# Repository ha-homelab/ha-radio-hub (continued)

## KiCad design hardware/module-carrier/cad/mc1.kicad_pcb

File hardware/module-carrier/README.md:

# MC1 hardware

> **Historical MC1 revision.** The current [MC2 external-antenna build](../../docs/external-antennas.md) uses different modules, pins, flash layout and housing. Keep this material with MC1 boards only.

> **I²C correction, 20 October 2026:** the current MC1 firmware now requires
> DFR0627 **A1=1/A0=0**, UART1 **0x50/0x51**; reserve **0x50–0x57**.
> Older frozen drawings/ledgers showing A1=A0=1 conflict with BME680 at0x77.
> Use the corrected switch setting; carrier copper does not change.

MC1 is the project's **single current custom PCB**: a carrier for finished
S3, H2, MG24 and WIZ850io modules. Male module pins are soldered directly into
plated holes, with controllers on the room-facing front and Ethernet/male harness
headers on the ceiling-facing back. Female module sockets and hand-soldered bare RF modules are excluded.

Current PCB envelope: **47.5 mm horizontal × 75 mm vertical, two copper layers**.
H3 is the sole PCB retention hole. Split enclosure rails support the long edges;
a separate jack stop and cable restraint protect the WIZ header joints.
Actual area is 6.9% below the preceding four-hole board and 26.9% below the historical 65 × 75 mm carrier,
with the same seven function groups. [Equal-scale comparison](layout-comparison.svg).
The Nano pin map, shared Ethernet/CC1101 SPI and matching active firmware replace
the old full-size S3 assignments. The RJ45 opening remains outward-facing on the ceiling side.
Physical USB shells remain included in the fit checks. Program before soldering;
normal updates use the network. H2 v1.3 requires R7 isolation and RX23/TX24 firmware.
Seven male headers are fitted on the back; J8/J9 remain unpopulated local recovery pads.
The five axial parts also mount on the back. Solder the entire back first,
including WIZ, inspect its joints, then fit and solder front U1–U3. Use both assembly drawings and the
[clearance and soldering study](studies/two-sided/assembly-review.md).

Use the [carrier enclosure prototype](../../mechanical/module-carrier/enclosure-prototype/README.md),
[single-anchor rail study](../../mechanical/module-carrier/rail-mount/README.md),
[visual guide](index.html), [assembly instructions](../../docs/module-carrier.md),
[CAD source](cad/), [gallery](images/README.md), and
[matching firmware](../../firmware/module-carrier/README.md) together.

The enclosure prototype has four printable parts: base, cover, trial jack stop
and required 4 mm ceiling spacing frame. Its shell is **84.3 × 121.8 × 57.4 mm**;
installed depth is **61.4 mm**. Fit floor hardware on the bench before ceiling
attachment and verify underside projection is no greater than 3 mm. Actual
module heights, jack contact and printed fit remain to be measured.

The schematic and PCB remain engineering prototypes. CAD and firmware checks do
not establish hardware operation, EMC/RF behavior, power margin or module fit.
An unverified manufacturing output must not be described as production-ready.

The current design is recorded in [designs.json](../designs.json). Earlier
boards are [historical references](../../docs/design-history.md), not alternative
current BOMs.

The [cost review](cost-review/README.md) records the provisional **$5.20 / five
bare boards** and **$55–57 populated-carrier materials** references. They exclude
shipping, tax, labor, enclosure and external modules; they are not a complete-hub
quotation. The [circuit schematic](cad/schematic.svg), [pin wiring](wiring.json) and
[connector ledger](cad/connectors.json) complement the front/back drawings.

Regenerate the presentation with `python3 hardware/module-carrier/render.py`.
The CAD and firmware directories document their separate validation commands.

Current evidence: [native checks](cad/verification.json),
[combined summary](verification-summary.json),
[independent review](independent-review.md), and
[visual migration](visual-migration.json).

Run `python3 -m unittest discover -s hardware/module-carrier -p "test_*.py"`
for the cross-file interface contract and `python3 hardware/module-carrier/render_board.py --check`
to verify native-render provenance.

The [square-layout](studies/square-layout/index.html),
[compact-host](studies/compact-s3/index.html) and
[SMLIGHT](studies/slzb-thread/index.html) studies are historical decision records.
Their selected direction is implemented here; their old build artifacts are not
substitutes for the active firmware or routed CAD.

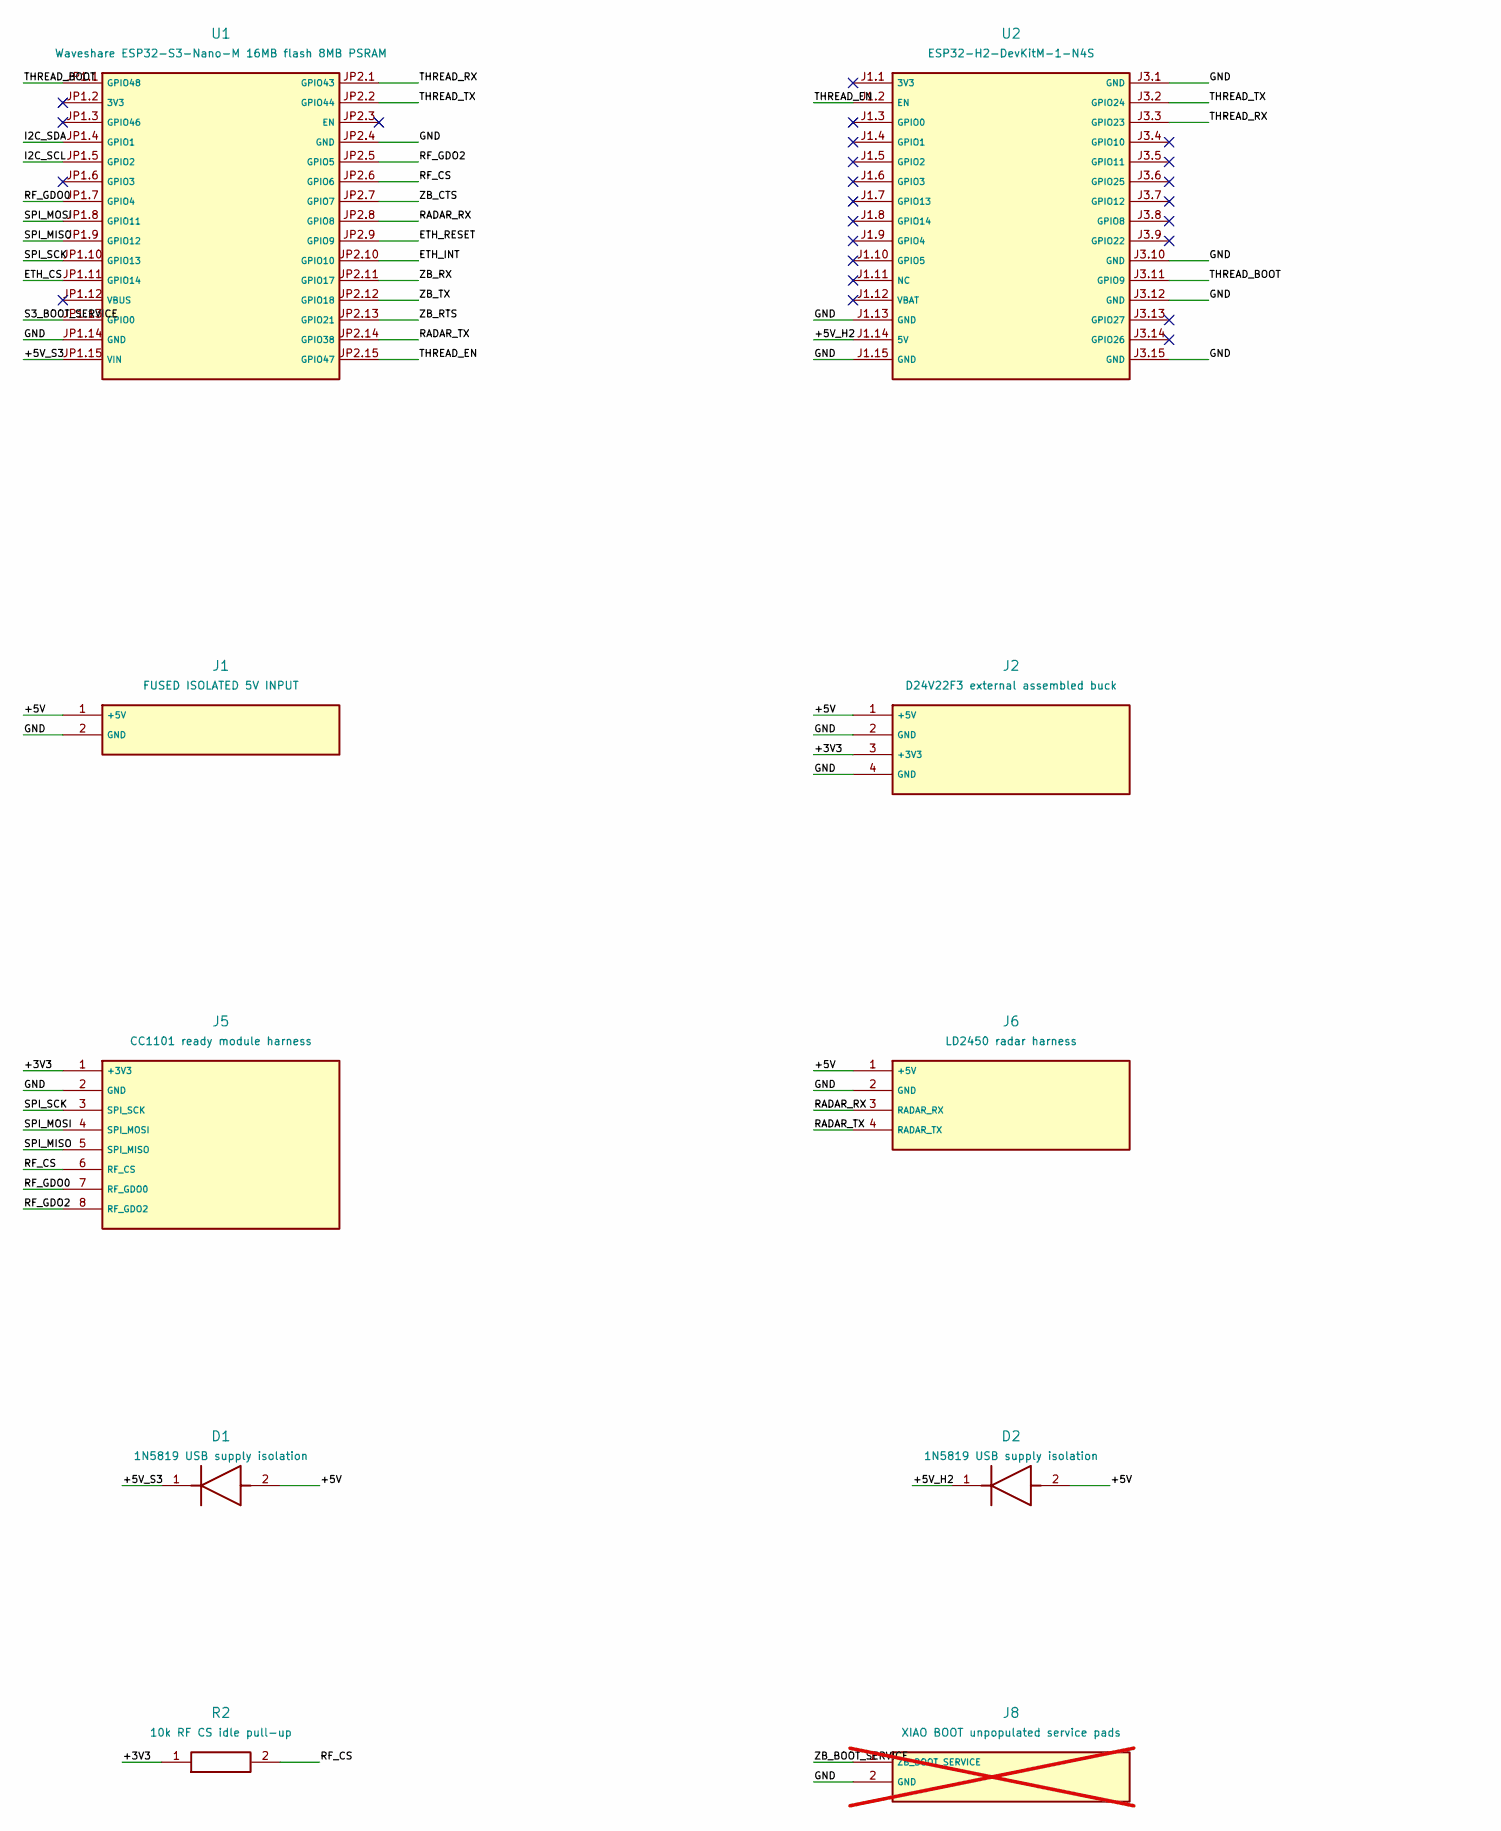
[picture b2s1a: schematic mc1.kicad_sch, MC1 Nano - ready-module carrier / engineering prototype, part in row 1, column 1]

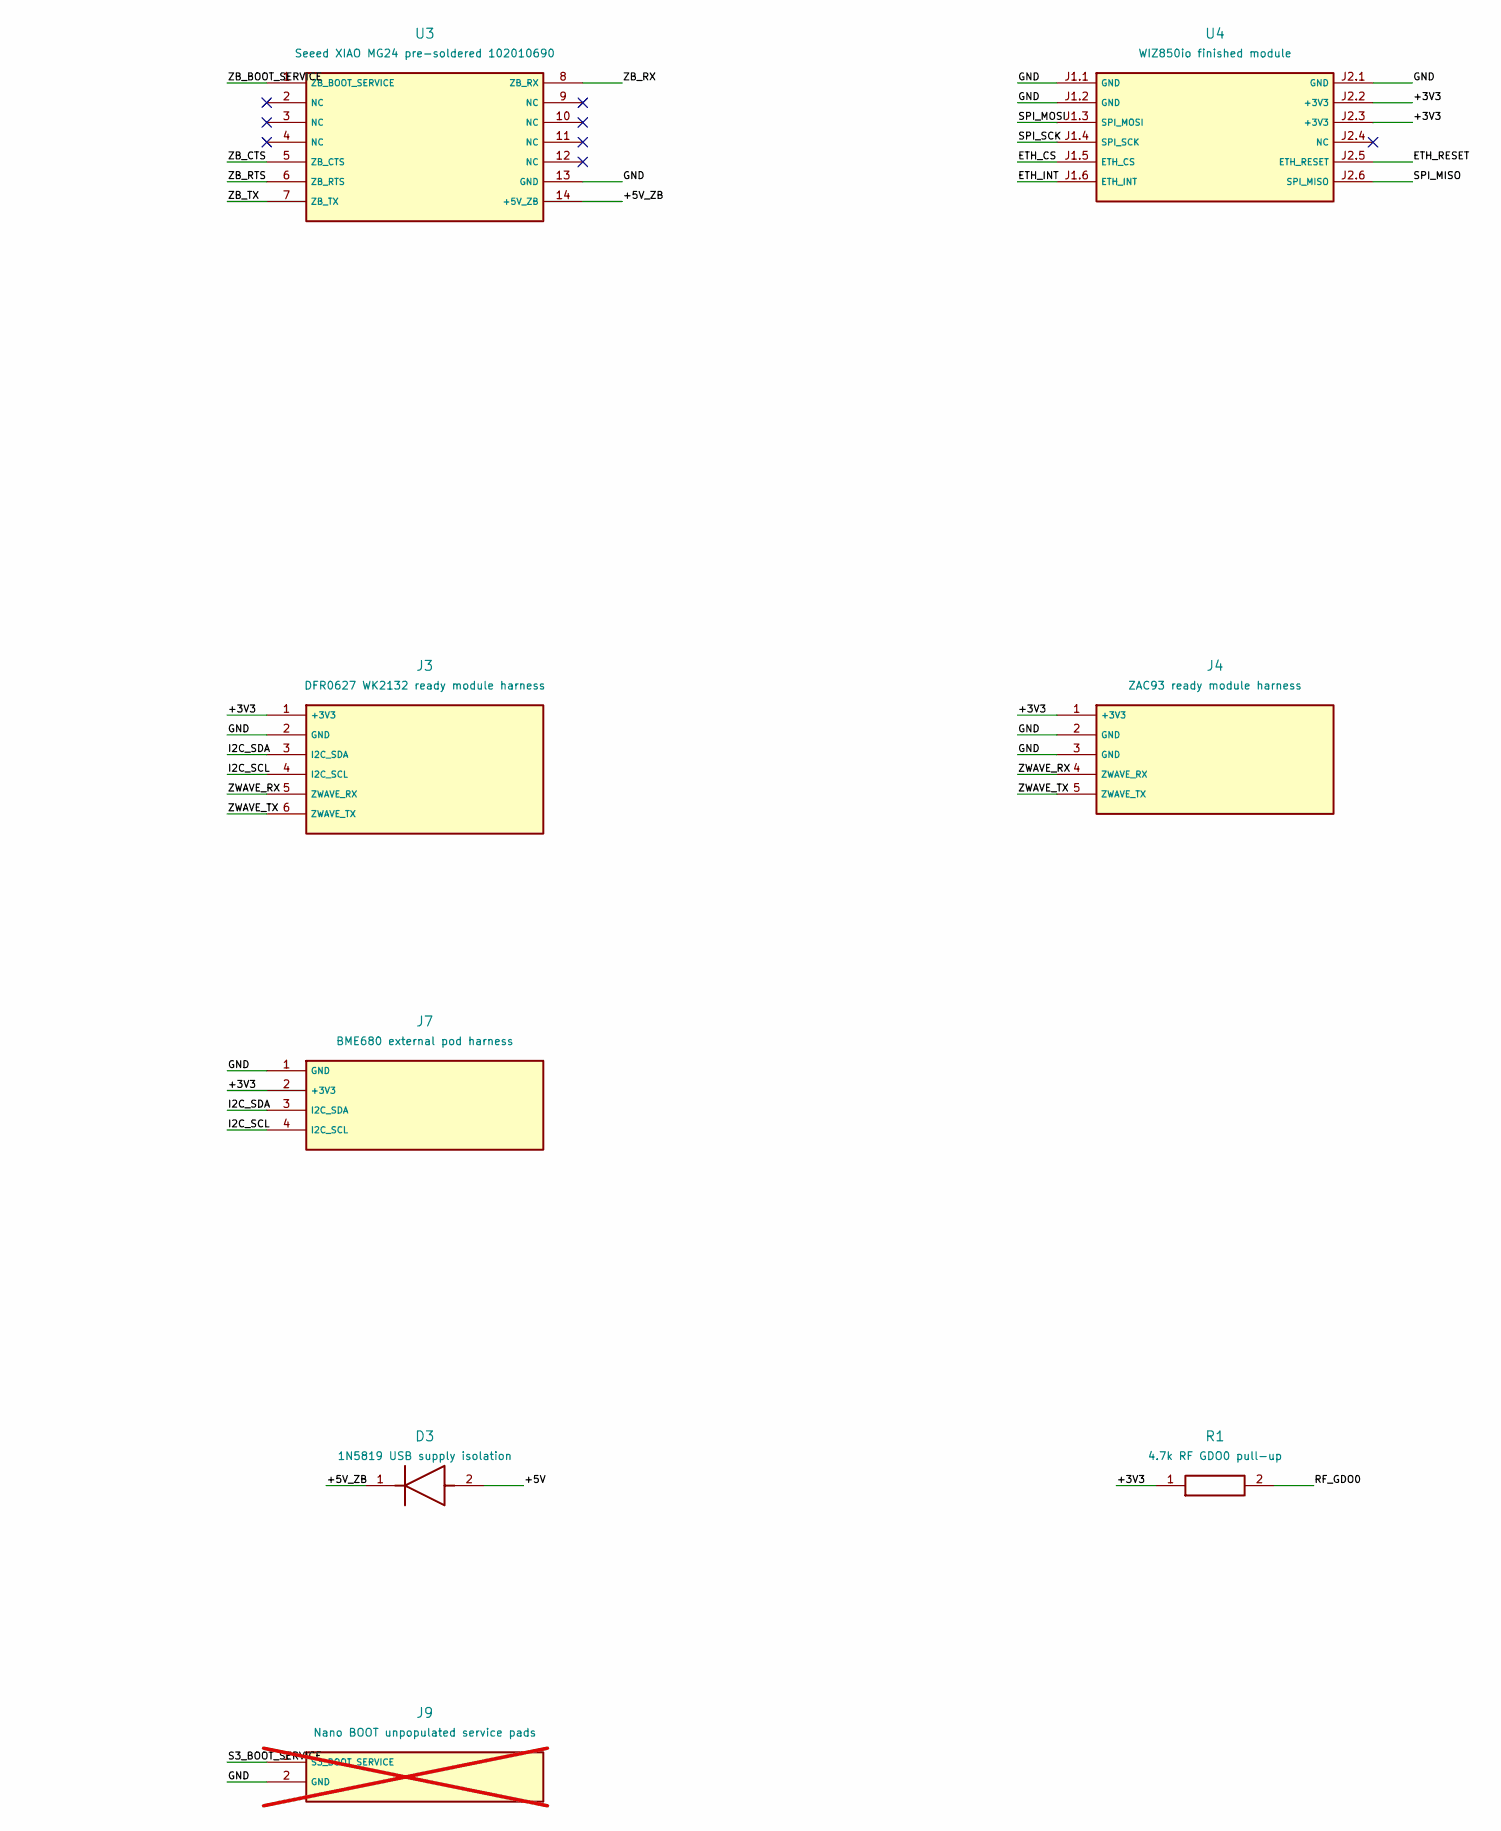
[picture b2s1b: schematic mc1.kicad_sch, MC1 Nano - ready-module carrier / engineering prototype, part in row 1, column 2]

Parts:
D1, D2, D3: 1N5819 USB supply isolation; D_DO-41_SOD81_P7.62mm_Horizontal
J1: FUSED ISOLATED 5V INPUT; PinHeader_1x02_P2.54mm_Vertical
J2: D24V22F3 external assembled buck; PinHeader_1x04_P2.54mm_Vertical
J3: DFR0627 WK2132 ready module harness; PinHeader_1x06_P2.54mm_Vertical
J4: ZAC93 ready module harness; PinHeader_1x05_P2.54mm_Vertical
J5: CC1101 ready module harness; PinHeader_1x08_P2.54mm_Vertical
J6: LD2450 radar harness; PinHeader_1x04_P2.54mm_Vertical
J7: BME680 external pod harness; PinHeader_1x04_P2.54mm_Vertical
J8: XIAO BOOT unpopulated service pads; PinHeader_1x02_P2.54mm_Vertical; not fitted
J9: Nano BOOT unpopulated service pads; PinHeader_1x02_P2.54mm_Vertical; not fitted
R1: 4.7k RF GDO0 pull-up; R_Axial_DIN0207_L6.3mm_D2.5mm_P7.62mm_Horizontal
R2: 10k RF CS idle pull-up; R_Axial_DIN0207_L6.3mm_D2.5mm_P7.62mm_Horizontal
U1: Waveshare ESP32-S3-Nano-M 16MB flash 8MB PSRAM; S3_Nano_M
U2: ESP32-H2-DevKitM-1-N4S; H2_DevKitM1
U3: Seeed XIAO MG24 pre-soldered 102010690; XIAO_MG24
U4: WIZ850io finished module; WIZ850io

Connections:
/+3V3: J2.3 (+3V3), J3.1 (+3V3), J4.1 (+3V3), J5.1 (+3V3), J7.2 (+3V3), R1.1, R2.1, U4.J2.2 (+3V3), U4.J2.3 (+3V3)
/+5V: D1.2, D2.2, D3.2, J1.1 (+5V), J2.1 (+5V), J6.1 (+5V)
/+5V_H2: D2.1, U2.J1.14 (5V)
/+5V_S3: D1.1, U1.JP1.15 (VIN)
/+5V_ZB: D3.1, U3.14 (+5V_ZB)
/ETH_CS: U1.JP1.11 (GPIO14), U4.J1.5 (ETH_CS)
/ETH_INT: U1.JP2.10 (GPIO10), U4.J1.6 (ETH_INT)
/ETH_RESET: U1.JP2.9 (GPIO9), U4.J2.5 (ETH_RESET)
/GND: J1.2 (GND), J2.2 (GND), J2.4 (GND), J3.2 (GND), J4.2 (GND), J4.3 (GND), J5.2 (GND), J6.2 (GND), J7.1 (GND), J8.2 (GND), J9.2 (GND), U1.JP1.14 (GND), U1.JP2.4 (GND), U2.J1.13 (GND), U2.J1.15 (GND), U2.J3.1 (GND), U2.J3.10 (GND), U2.J3.12 (GND), U2.J3.15 (GND), U3.13 (GND), U4.J1.1 (GND), U4.J1.2 (GND), U4.J2.1 (GND)
/I2C_SCL: J3.4 (I2C_SCL), J7.4 (I2C_SCL), U1.JP1.5 (GPIO2)
/I2C_SDA: J3.3 (I2C_SDA), J7.3 (I2C_SDA), U1.JP1.4 (GPIO1)
/RADAR_RX: J6.3 (RADAR_RX), U1.JP2.8 (GPIO8)
/RADAR_TX: J6.4 (RADAR_TX), U1.JP2.14 (GPIO38)
/RF_CS: J5.6 (RF_CS), R2.2, U1.JP2.6 (GPIO6)
/RF_GDO0: J5.7 (RF_GDO0), R1.2, U1.JP1.7 (GPIO4)
/RF_GDO2: J5.8 (RF_GDO2), U1.JP2.5 (GPIO5)
/S3_BOOT_SERVICE: J9.1 (S3_BOOT_SERVICE), U1.JP1.13 (GPIO0)
/SPI_MISO: J5.5 (SPI_MISO), U1.JP1.9 (GPIO12), U4.J2.6 (SPI_MISO)
/SPI_MOSI: J5.4 (SPI_MOSI), U1.JP1.8 (GPIO11), U4.J1.3 (SPI_MOSI)
/SPI_SCK: J5.3 (SPI_SCK), U1.JP1.10 (GPIO13), U4.J1.4 (SPI_SCK)
/THREAD_BOOT: U1.JP1.1 (GPIO48), U2.J3.11 (GPIO9)
/THREAD_EN: U1.JP2.15 (GPIO47), U2.J1.2 (EN)
/THREAD_RX: U1.JP2.1 (GPIO43), U2.J3.3 (GPIO23)
/THREAD_TX: U1.JP2.2 (GPIO44), U2.J3.2 (GPIO24)
/ZB_BOOT_SERVICE: J8.1 (ZB_BOOT_SERVICE), U3.1 (ZB_BOOT_SERVICE)
/ZB_CTS: U1.JP2.7 (GPIO7), U3.5 (ZB_CTS)
/ZB_RTS: U1.JP2.13 (GPIO21), U3.6 (ZB_RTS)
/ZB_RX: U1.JP2.11 (GPIO17), U3.8 (ZB_RX)
/ZB_TX: U1.JP2.12 (GPIO18), U3.7 (ZB_TX)
/ZWAVE_RX: J3.5 (ZWAVE_RX), J4.4 (ZWAVE_RX)
/ZWAVE_TX: J3.6 (ZWAVE_TX), J4.5 (ZWAVE_TX)

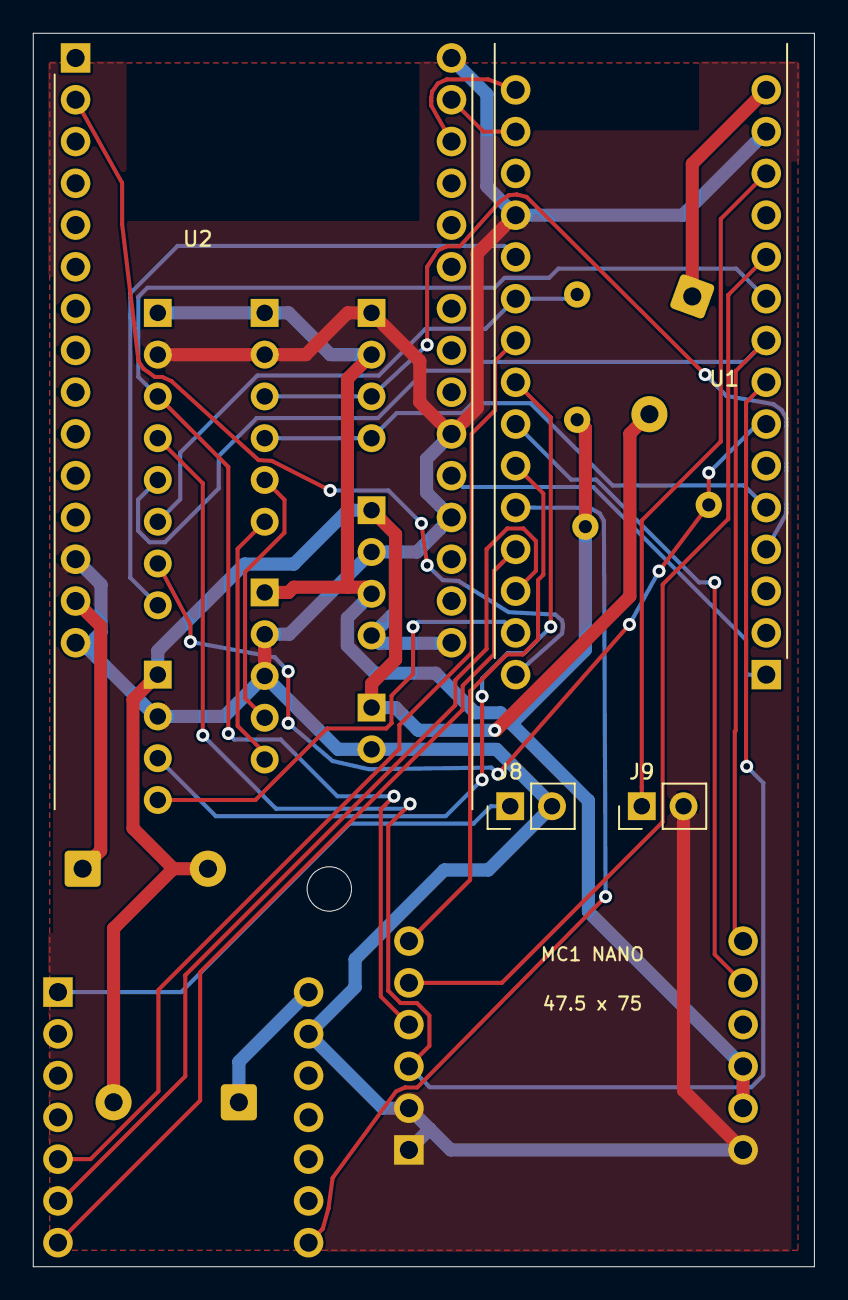
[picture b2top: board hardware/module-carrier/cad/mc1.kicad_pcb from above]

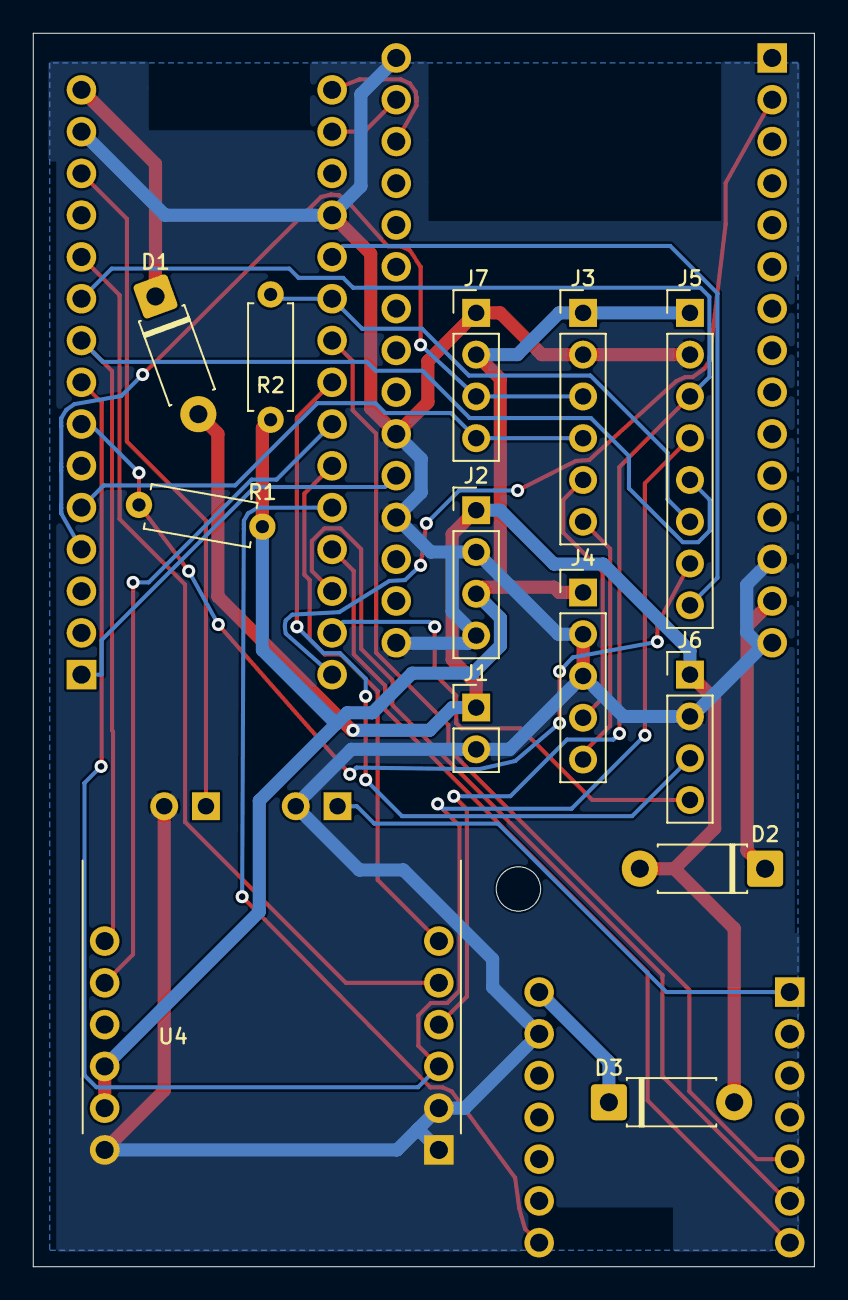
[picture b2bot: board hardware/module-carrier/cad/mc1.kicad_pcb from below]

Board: 2 copper layers, 47.5 x 75.0 mm, 19 parts (13 on the bottom side), 31 nets.

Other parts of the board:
H3: M2.5 NYLON NPTH

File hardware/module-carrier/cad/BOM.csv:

Reference,Quantity,Fitted,Part / module,Carrier footprint,Side,Assembly note,Source
U1,1,true,Waveshare ESP32-S3-Nano-M 16MB flash 8MB PSRAM,MC1:S3_Nano_M,Front,Factory male pins direct solder; JP1.15 VIN via D1; VBUS/3V3 NC; nativeUSB19/20; GPIO0 service; sharedSPI; no sockets,https://docs.waveshare.com/ESP32-S3-Nano
U2,1,true,ESP32-H2-DevKitM-1-N4S,MC1:H2_DevKitM1,Front,RCP/ROM RX23 TX24; remove USB-UART TX series R7 before assembly; native USB retained; 3V3/VBAT NC,https://dl.espressif.com/dl/schematics/esp32-h2-devkitm-1_v1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
U3,1,true,Seeed XIAO MG24 pre-soldered 102010690,MC1:XIAO_MG24,Front,External UART PC06/PC07; CTS PC04 RTS PC05; USB probe preserved; 3V3 OUT NC,https://files.seeedstudio.com/wiki/XIAO_MG24/Getting_Start/X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
U4,1,true,WIZ850io finished module,MC1:WIZ850io,Back,Direct factory pins; two1x6 at20.32 rowspacing; RJ45 faces BOTTOM with mouth y=77mm; NO PoE extraction;3.3V only,https://docs.wiznet.io/img/products/wiz850io/wiz850io_dimension.png
J1,1,true,FUSED ISOLATED 5V INPUT,MC1:PinHeader_1x02_P2.54mm_Vertical,Back,Offboard assembled active PoE splitter and fused 5V harness. No raw PoE voltage on carrier.,https://www.samtec.com/products/tsw
J2,1,true,D24V22F3 external assembled buck,MC1:PinHeader_1x04_P2.54mm_Vertical,Back,Harness interface only; pin1 buckVIN; pin2GND;pin3buckVOUT;pin4GND. Buck remains separate ready module.,https://www.samtec.com/products/tsw
J3,1,true,DFR0627 WK2132 ready module harness,MC1:PinHeader_1x06_P2.54mm_Vertical,Back,"Harness to DFR0627 I2C and UART1, no WK2132 SMD on carrier. J3.5=module TX1;J3.6=module RX1; IA1=1 IA0=1; register address 0x70, FIFO 0x71; verify physical markings.",https://wiki.dfrobot.com/dfr0627
J4,1,true,ZAC93 ready module harness,MC1:PinHeader_1x05_P2.54mm_Vertical,Back,Carrier1->ZACpin1;2->pin6;3->pin9;4->pin8RX;5->pin10TX. Different from ZAC physical header layout.,https://www.samtec.com/products/tsw
J5,1,true,CC1101 ready module harness,MC1:PinHeader_1x08_P2.54mm_Vertical,Back,3.3V; GDO0 open-drain TX with external4.7k pullup; GDO2 receiver.,https://www.samtec.com/products/tsw
J6,1,true,LD2450 radar harness,MC1:PinHeader_1x04_P2.54mm_Vertical,Back,Carrier3->radarRX;carrier4<-radarTX;5V supply;3.3V data.,https://www.samtec.com/products/tsw
J7,1,true,BME680 external pod harness,MC1:PinHeader_1x04_P2.54mm_Vertical,Back,"External pod,1GND2VDD3SDA4SCL;I2C pullups on modules;do notaddunreviewedpullups.",https://www.samtec.com/products/tsw
D1,1,true,1N5819 USB supply isolation,MC1:D_DO-41_SOD81_P7.62mm_Horizontal,Back,Cathodepad1->board5V;anodepad2->fused5Vbus. VerifyUSBprogrammingpowerpaths;forwarddropheadroom.,https://www.vishay.com/docs/88525/1n5817.pdf
D2,1,true,1N5819 USB supply isolation,MC1:D_DO-41_SOD81_P7.62mm_Horizontal,Back,Cathodepad1->board5V;anodepad2->fused5Vbus. VerifyUSBprogrammingpowerpaths;forwarddropheadroom.,https://www.vishay.com/docs/88525/1n5817.pdf
D3,1,true,1N5819 USB supply isolation,MC1:D_DO-41_SOD81_P7.62mm_Horizontal,Back,Cathodepad1->board5V;anodepad2->fused5Vbus. VerifyUSBprogrammingpowerpaths;forwarddropheadroom.,https://www.vishay.com/docs/88525/1n5817.pdf
R1,1,true,4.7k RF GDO0 pull-up,MC1:R_Axial_DIN0207_L6.3mm_D2.5mm_P7.62mm_Horizontal,Back,,https://www.vishay.com/docs/28729/mrs16.pdf
R2,1,true,10k RF CS idle pull-up,MC1:R_Axial_DIN0207_L6.3mm_D2.5mm_P7.62mm_Horizontal,Back,,https://www.vishay.com/docs/28729/mrs16.pdf
J8,0,false,XIAO BOOT unpopulated service pads,MC1:PinHeader_1x02_P2.54mm_Vertical,Front,Temporary short D0/PC00 to GND while resetting XIAO for recovery. Normally OPEN.,https://www.samtec.com/products/tsw
J9,0,false,Nano BOOT unpopulated service pads,MC1:PinHeader_1x02_P2.54mm_Vertical,Front,Normally OPEN; short GPIO0 to GND while pressing Nano RESET for nativeUSB ROM recovery.,https://www.samtec.com/products/tsw

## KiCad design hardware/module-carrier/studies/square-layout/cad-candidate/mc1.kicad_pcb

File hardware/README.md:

# HA Radio Hub hardware platform

<!-- MC2-CURRENT-DESIGN -->
> **Current build: [MC2 — three external antennas](../docs/external-antennas.md).** This page retains an earlier design or evaluation for reference. Its board images, pin maps, enclosure fit and alternative BOMs are not the current MC2 build.

This is the original Pi-based reference. The newer **single-S3** architecture,
custom PCBs and graphical connector maps are in [low-power hardware](low-power/README.md).

Design prototype, revision A. Component selection against documentation was checked on 2026-10-16; combined hardware operation, thermal performance and fit have not yet been measured. This is an assembly of off-the-shelf modules, not a designed or certified PCB.

## Selected architecture

One external Cat5e/Cat6 cable carries Ethernet and power from an **active IEEE 802.3at PoE+** port. An isolated splitter supplies 5 V. Its Ethernet output connects to an internal 100 Mbps switch. Raspberry Pi 4 runs OTBR locally and exposes a separate Zigbee NCP to ZHA over TCP. The Raspberry Pi is not the Home Assistant server: HA stays on the existing server.

- **Zigbee:** SMLIGHT SLZB-07Mg24, a dedicated EFR32MG24 running as a Zigbee NCP, connected to the Pi by USB. Added to HA as a ZHA network adapter. No MultiPAN.
- **Thread:** a separate Nordic nRF52840 Dongle PCA10059 running OpenThread RCP over USB. OTBR runs on the Pi inside the enclosure. HA uses the OpenThread Border Router, Thread and Matter integrations.
- **BLE + Z-Wave + sensors:** Waveshare ESP32-S3-ETH-M with W5500, connected to the switch by Ethernet. ESPHome handles the Bluetooth proxy, ZAC93 UART, LD2450 UART and BME680 I²C together. This is the intended combined configuration; operation under simultaneous load requires bench testing.
- **RF:** the fully wired option uses a second ESP32-S3-ETH-M + CC1101 433.92 MHz on Ethernet port 4, with separate GDO0/TX and GDO2/RX. The firmware ports MQTT/API, RM433 and Dooya from RF Airbridge; hardware testing and migration of private settings remain necessary before replacing the active node. The **compatibility option** retains the old ESP8266 NodeMCU + CC1101 inside the enclosure, but still uses Wi-Fi and does not meet the all-wired requirement. Choose one RF branch; do not install both as identical event sources. See [RF migration](rf-migration.md).
- **LD2450:** a 24 GHz radar on the front wall. The number 2450 is the model name, not a frequency of 2.450 GHz.
- **BME680:** a separate ventilated mini-enclosure on a short I²C cable, outside the hot Pi/switch compartment.

The ESP32-C5 from the original example is not in the baseline BOM: Linux OTBR + a dedicated RCP provide a reproducible route on a documented platform. A Thread radio chip alone does not make a board a border router.

## Parts and dimensions

[Block diagram](wiring.svg) · [BOM CSV](bom.csv) lists exact selected models, fastener/cable requirements, sources and status. BOM prices are budget estimates, not vendor quotations; availability was not researched for entries without a price. Existing ZAC93 and NodeMCU/CC1101 hardware can be reused.

The [procurement and order checklist](procurement.md) defines the fully wired assembly, separate mating connectors and checks for the selected power parts. The BOM is for buying prototype parts: it does not mean that a particular USB-C cable, DC plug or fuse set has already been tested. Adafruit 4536 for the Pi remains a candidate without a published 3 A rating; C10/C11 require mating-connector checks.

Main dimensions for layout:

- Pi 4: 85 × 56 mm PCB; allow for a heatsink and microSD access.
- TL-SF1005D v13: 104 × 70 × 22 mm enclosure; cable plugs extend beyond these dimensions.
- PoE splitter: 102.5 × 29.6 × 24.8 mm, excluding cable bends.
- ESP32-S3-ETH: 72.8 × 21 mm in plan according to the [Waveshare drawing](https://docs.waveshare.com/assets/images/ESP32-S3-ETH-details-size-e17a2432fc60e98e2ed27afcdbea08cc.webp). Measure the height with soldered headers and connected plugs. USB radios, ZAC93 and NodeMCU: reserved spaces include margin; check exact connector heights and mounting pitches on the delivered parts.
- Project enclosure: nominally 240 × 200 × 80 mm, with two levels. Assembly fit has not been verified. Do not print the final enclosure before checking cable fit.

Off-the-shelf alternatives include a desktop ABS/polycarbonate box with at least 240 × 200 × 80 mm of clear **internal** space, or a DIN enclosure with a separate RF compartment. External dimensions do not prove sufficient room: standoffs, the lid and cable entries reduce usable space, so the layout must be checked again. A metal enclosure is suitable only with external antennas; the built-in Nordic and ZAC93 antennas will lose efficiency inside metal. This revision favors a printed PETG/ASA enclosure with a replaceable mounting deck.

## Power and assembly

Follow the [wiring instructions](wiring.md) and [power budget](power.md). Do not infer an unknown module pinout from wire colors. ZAC93 and CC1101 use **3.3 V** power and logic; LD2450 uses **5 V** power and **3.3 V** UART logic. All low-voltage grounds join after the isolated splitter; assembly does not modify the PoE input or network pairs.

Assembly order: splitter and distribution → switch/Pi → separate USB radios → ESP32 Ethernet → LD2450 → ZAC93 → BME680 → RF. At each step, measure voltage at the module itself and test it individually. Connect UART and I²C wiring with power off. During normal operation, each module has only one power source; disconnect its 5 V branch before connecting a USB programmer.

## RF layout

See [antennas and coexistence](antennas.md). Place the enclosure centrally, while ensuring that LD2450 faces the monitored room and BME680 samples ambient air. These requirements can conflict, which is why modular external mounts are provided.

A successful compile is not the readiness criterion: acceptance requires 5 V measurements under load, 24–72 h of combined operation, recovery after a PoE power cycle, Zigbee/Thread traffic, BLE connections, Z-Wave inclusion and RF reception/transmission with a real device.

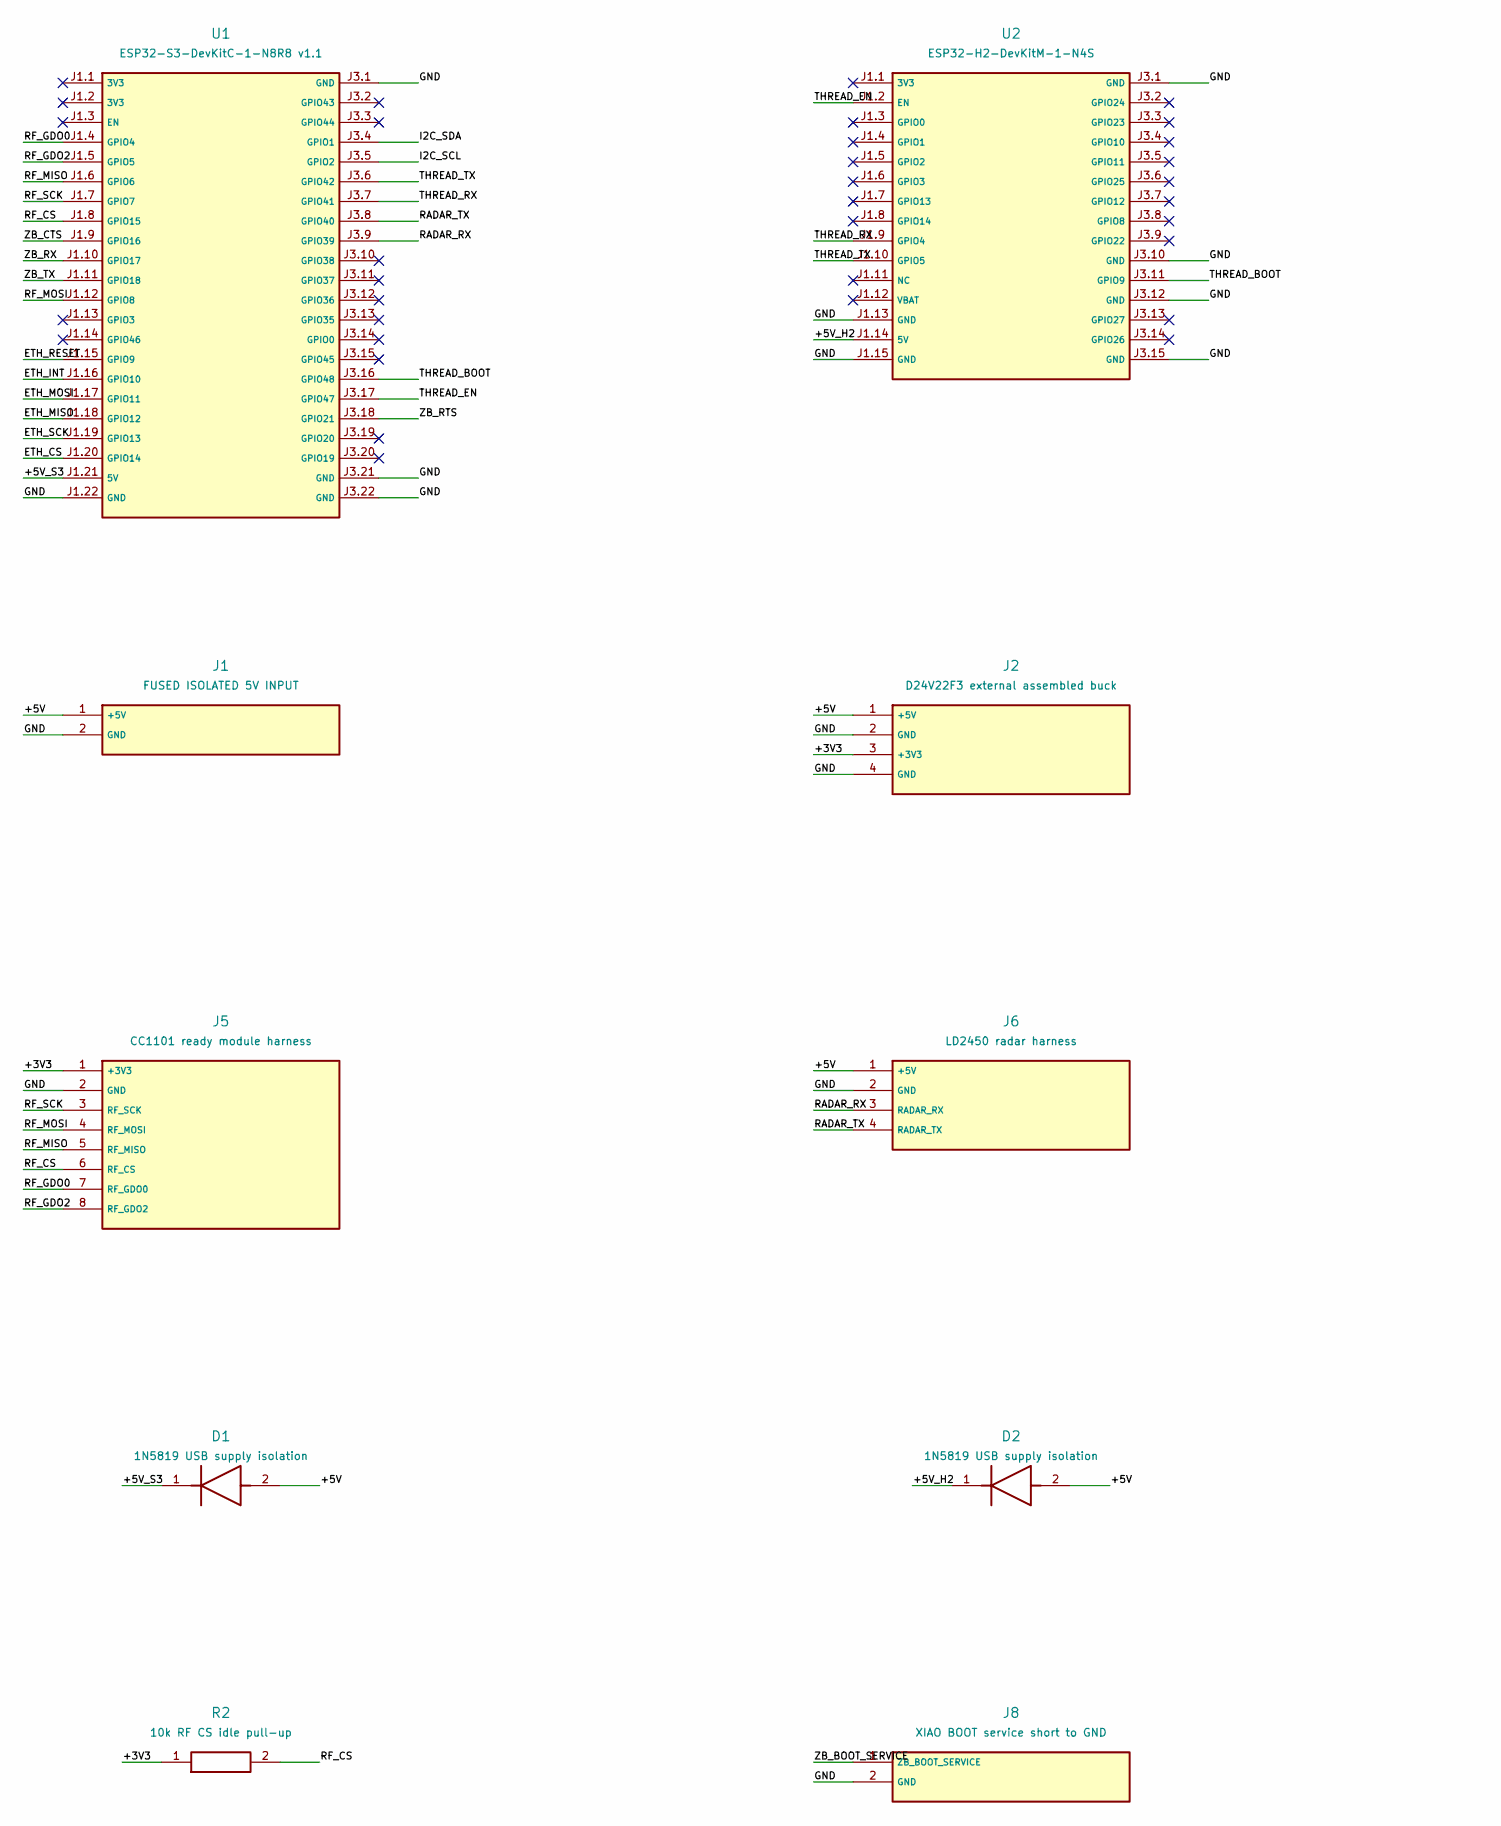
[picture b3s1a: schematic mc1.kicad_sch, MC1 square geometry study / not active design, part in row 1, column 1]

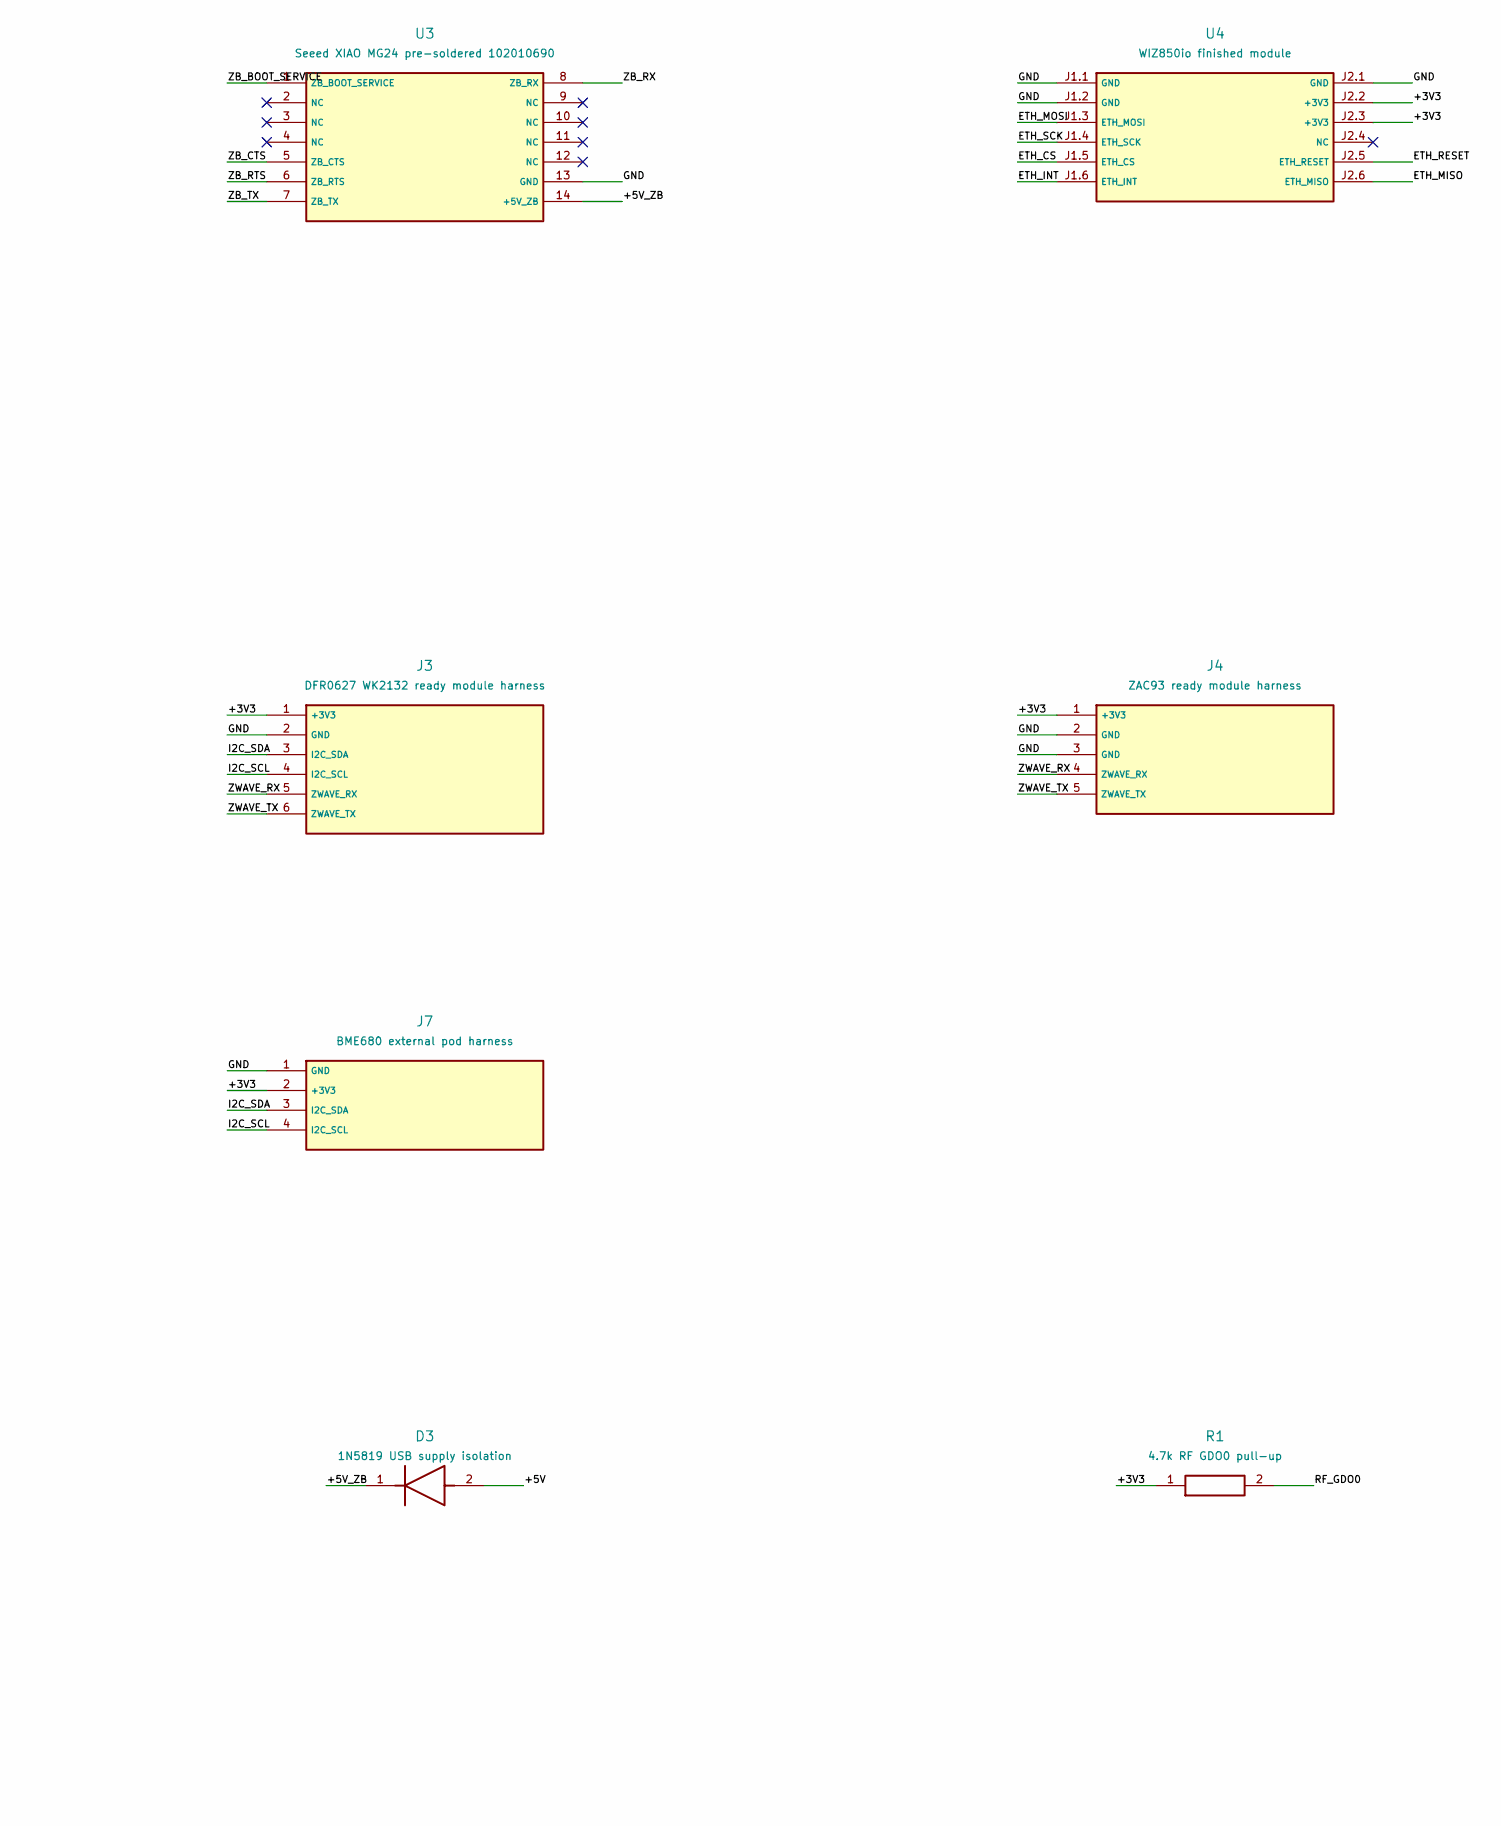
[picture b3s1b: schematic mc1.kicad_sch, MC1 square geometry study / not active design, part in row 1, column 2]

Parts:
D1, D2, D3: 1N5819 USB supply isolation; D_DO-41_SOD81_P7.62mm_Horizontal
J1: FUSED ISOLATED 5V INPUT; PinHeader_1x02_P2.54mm_Vertical
J2: D24V22F3 external assembled buck; PinHeader_1x04_P2.54mm_Vertical
J3: DFR0627 WK2132 ready module harness; PinHeader_1x06_P2.54mm_Vertical
J4: ZAC93 ready module harness; PinHeader_1x05_P2.54mm_Vertical
J5: CC1101 ready module harness; PinHeader_1x08_P2.54mm_Vertical
J6: LD2450 radar harness; PinHeader_1x04_P2.54mm_Vertical
J7: BME680 external pod harness; PinHeader_1x04_P2.54mm_Vertical
J8: XIAO BOOT service short to GND; PinHeader_1x02_P2.54mm_Vertical
R1: 4.7k RF GDO0 pull-up; R_Axial_DIN0207_L6.3mm_D2.5mm_P7.62mm_Horizontal
R2: 10k RF CS idle pull-up; R_Axial_DIN0207_L6.3mm_D2.5mm_P7.62mm_Horizontal
U1: ESP32-S3-DevKitC-1-N8R8 v1.1; S3_DevKitC1_v11
U2: ESP32-H2-DevKitM-1-N4S; H2_DevKitM1
U3: Seeed XIAO MG24 pre-soldered 102010690; XIAO_MG24
U4: WIZ850io finished module; WIZ850io

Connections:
/+3V3: J2.3 (+3V3), J3.1 (+3V3), J4.1 (+3V3), J5.1 (+3V3), J7.2 (+3V3), R1.1, R2.1, U4.J2.2 (+3V3), U4.J2.3 (+3V3)
/+5V: D1.2, D2.2, D3.2, J1.1 (+5V), J2.1 (+5V), J6.1 (+5V)
/+5V_H2: D2.1, U2.J1.14 (5V)
/+5V_S3: D1.1, U1.J1.21 (5V)
/+5V_ZB: D3.1, U3.14 (+5V_ZB)
/ETH_CS: U1.J1.20 (GPIO14), U4.J1.5 (ETH_CS)
/ETH_INT: U1.J1.16 (GPIO10), U4.J1.6 (ETH_INT)
/ETH_MISO: U1.J1.18 (GPIO12), U4.J2.6 (ETH_MISO)
/ETH_MOSI: U1.J1.17 (GPIO11), U4.J1.3 (ETH_MOSI)
/ETH_RESET: U1.J1.15 (GPIO9), U4.J2.5 (ETH_RESET)
/ETH_SCK: U1.J1.19 (GPIO13), U4.J1.4 (ETH_SCK)
/GND: J1.2 (GND), J2.2 (GND), J2.4 (GND), J3.2 (GND), J4.2 (GND), J4.3 (GND), J5.2 (GND), J6.2 (GND), J7.1 (GND), J8.2 (GND), U1.J1.22 (GND), U1.J3.1 (GND), U1.J3.21 (GND), U1.J3.22 (GND), U2.J1.13 (GND), U2.J1.15 (GND), U2.J3.1 (GND), U2.J3.10 (GND), U2.J3.12 (GND), U2.J3.15 (GND), U3.13 (GND), U4.J1.1 (GND), U4.J1.2 (GND), U4.J2.1 (GND)
/I2C_SCL: J3.4 (I2C_SCL), J7.4 (I2C_SCL), U1.J3.5 (GPIO2)
/I2C_SDA: J3.3 (I2C_SDA), J7.3 (I2C_SDA), U1.J3.4 (GPIO1)
/RADAR_RX: J6.3 (RADAR_RX), U1.J3.9 (GPIO39)
/RADAR_TX: J6.4 (RADAR_TX), U1.J3.8 (GPIO40)
/RF_CS: J5.6 (RF_CS), R2.2, U1.J1.8 (GPIO15)
/RF_GDO0: J5.7 (RF_GDO0), R1.2, U1.J1.4 (GPIO4)
/RF_GDO2: J5.8 (RF_GDO2), U1.J1.5 (GPIO5)
/RF_MISO: J5.5 (RF_MISO), U1.J1.6 (GPIO6)
/RF_MOSI: J5.4 (RF_MOSI), U1.J1.12 (GPIO8)
/RF_SCK: J5.3 (RF_SCK), U1.J1.7 (GPIO7)
/THREAD_BOOT: U1.J3.16 (GPIO48), U2.J3.11 (GPIO9)
/THREAD_EN: U1.J3.17 (GPIO47), U2.J1.2 (EN)
/THREAD_RX: U1.J3.7 (GPIO41), U2.J1.9 (GPIO4)
/THREAD_TX: U1.J3.6 (GPIO42), U2.J1.10 (GPIO5)
/ZB_BOOT_SERVICE: J8.1 (ZB_BOOT_SERVICE), U3.1 (ZB_BOOT_SERVICE)
/ZB_CTS: U1.J1.9 (GPIO16), U3.5 (ZB_CTS)
/ZB_RTS: U1.J3.18 (GPIO21), U3.6 (ZB_RTS)
/ZB_RX: U1.J1.10 (GPIO17), U3.8 (ZB_RX)
/ZB_TX: U1.J1.11 (GPIO18), U3.7 (ZB_TX)
/ZWAVE_RX: J3.5 (ZWAVE_RX), J4.4 (ZWAVE_RX)
/ZWAVE_TX: J3.6 (ZWAVE_TX), J4.5 (ZWAVE_TX)
